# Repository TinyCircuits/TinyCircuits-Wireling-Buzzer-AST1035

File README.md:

# TinyCircuits Wireling Buzzer
# AST1035 Rev1

The design files are located under design_files/ for the TinyCircuits AST1035 Rev 1 PCB. This is a whisker board which features a simple Electric buzzer to give your projects a voice in the form of a variety of tones.

Format is in Cadsoft Eagle format - Eagle version 6.2 was used for the original design.

For more infomation on this, check out the product page at TinyCircuits.com

# License:

Design by TinyCircuits.
All design files are released under the Creative Commons Attribution Share-Alike 3.0 License, see the following link for details: http://creativecommons.org/licenses/by-sa/3.0

All text above must be included in any redistribution or derived design

This project uses designs and concepts developed as part of the Arduino project and the LilyPad project.  The TinyCircuits design files themselves (schematics, PCB and libraries) are not directly derived from these works' design files and have been created new, however the concepts and basic architecture behind the TinyDuino and TinyLily products are derived and we thank the hard work of the organizations below for their contributions to open-source hardware:
  
Original Arduino Uno Design by Team Arduino

LilyPad Arduino Design by Leah Buechley and Sparkfun Electronics

Please support the open-source hardware community

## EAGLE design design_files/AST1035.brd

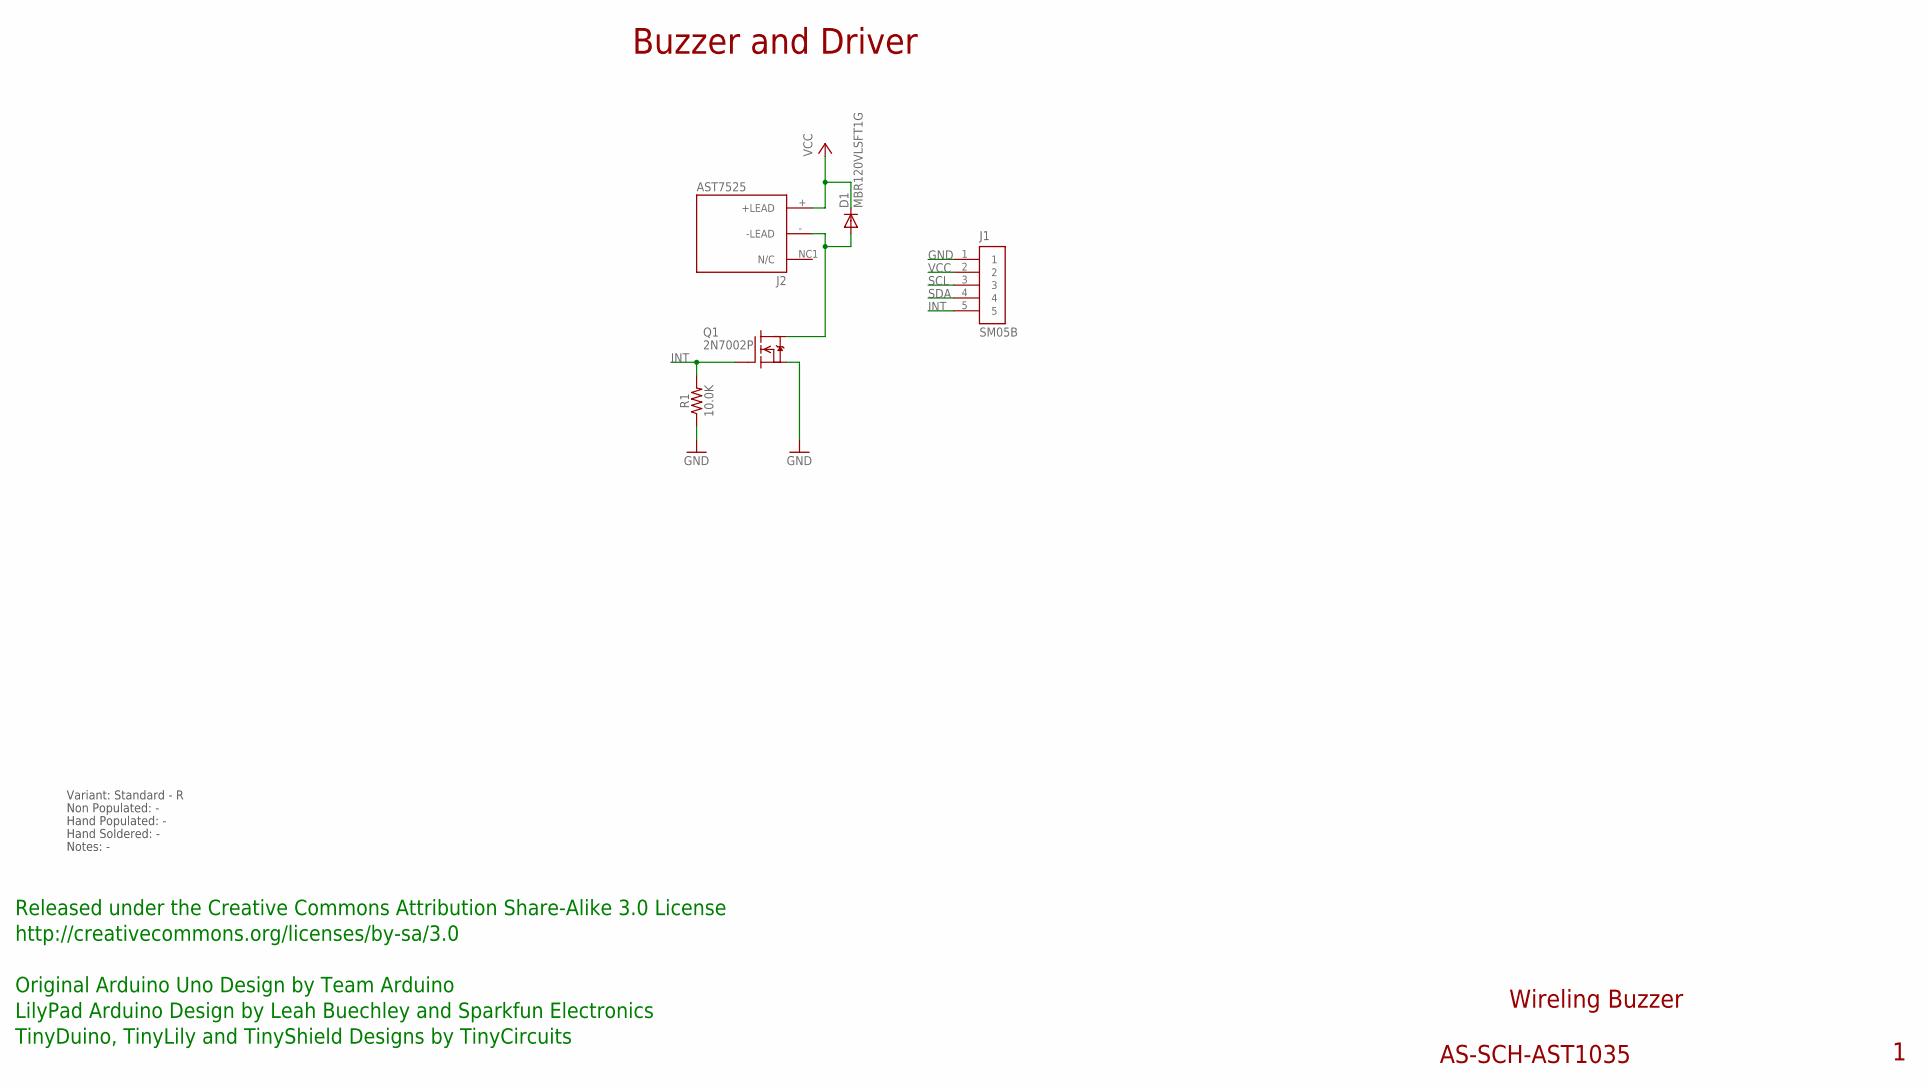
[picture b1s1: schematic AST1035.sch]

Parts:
D1: MBR120VLSFT1G; SOD-123FL
J1: SM05B; JST_SH_5X1_EDGE
J2: AST7525
Q1: 2N7002P; SOT23A
R1: 10.0K; 0402

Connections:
GND: J1.1, Q1.E (S), R1.1
INT: J1.5, Q1.B (G), R1.2
LOAD: D1.A, J2.- (-LEAD), Q1.C (D)
SCL: J1.3
SDA: J1.4
VCC: D1.C, J1.2, J2.+ (+LEAD)

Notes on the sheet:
Wireling Buzzer
AS-SCH-AST1035
Buzzer and Driver
Released under the Creative Commons Attribution Share-Alike 3.0 License
http://creativecommons.org/licenses/by-sa/3.0
Original Arduino Uno Design by Team Arduino
TinyDuino, TinyLily and TinyShield Designs by TinyCircuits
LilyPad Arduino Design by Leah Buechley and Sparkfun Electronics
Non Populated: -
Hand Populated: -
Hand Soldered: -
Notes: -
Variant: Standard - R

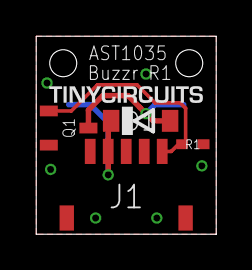
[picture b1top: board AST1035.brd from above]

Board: 2 copper layers, 10.0 x 11.0 mm, 6 parts (1 on the bottom side), 4 nets.

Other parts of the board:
U$1: DOCFIELD-TINYCIRCUITS-PCB

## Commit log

2019-08-05 added datasheet
2019-11-08 update naming
2019-12-03 images
2019-12-04 code
2020-02-04 mass image update
2020-02-29 made .zip for pitches download link
2020-08-14 Add CAD data
